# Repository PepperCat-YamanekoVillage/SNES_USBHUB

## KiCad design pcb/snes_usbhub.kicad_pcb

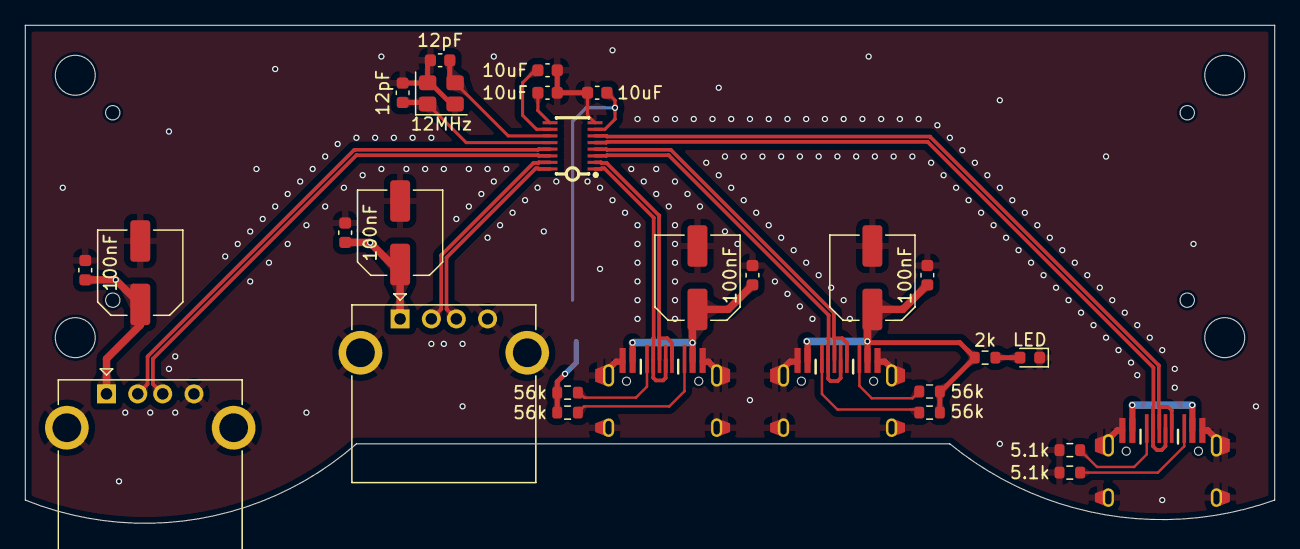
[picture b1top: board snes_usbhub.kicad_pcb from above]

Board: 2 copper layers, 100.0 x 39.9 mm, 36 parts (0 on the bottom side), 23 nets.

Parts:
C1, C3, C21, C23: 100uF; C_Elec_6.3x5.4
C2, C4, C29, C30: 100nF; C_0603_1608Metric
C5, C6: 12pF; C_0603_1608Metric
C7, C8, C9: 10uF; C_0603_1608Metric
D1: LED; LED_0603_1608Metric
H1, H2, H3, H4: MountingHole_3.2mm_M3_ISO7380
H5, H6, H7, H8: toolinghole
J1, J2, J3: USB_C_Connecter; usbc_hand
J8, J9: USB_A; USB_A_Kycon_KUSBX-AS1N-B_Horizontal
R1, R2, R3, R4: 56k; R_0603_1608Metric
R13: 2k; R_0603_1608Metric
R20, R21: 5.1k; R_0603_1608Metric
U3: SL2.1S; SSOP-16_L4.6-W2.6-P0.53-LS4.0-BL
Y1: 12MHz; Crystal_SMD_3225-4Pin_3.2x2.5mm

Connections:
+5V: C1.1, C2.2, C3.1, C4.2, C7.1, C21.1, C23.1, C29.2, C30.2, J1.A4 (VBUS), J2.A4 (VBUS), J3.A4 (VBUS), J8.1 (VBUS), J9.1 (VBUS), R1.2, R2.2, R3.2, R4.2, R13.1, U3.7 (VDD5)
/deviceA1/D+: J8.3 (D+), U3.16 (DP3)
/deviceA1/D-: J8.2 (D-), U3.15 (DM3)
/deviceA2/D+: J9.3 (D+), U3.14 (DP4)
/deviceA2/D-: J9.2 (D-), U3.13 (DM4)
/deviceC1/D+: J3.A6 (D+), J3.B6 (D+), U3.2 (DP2)
/deviceC1/D-: J3.A7 (D-), J3.B7 (D-), U3.1 (DM2)
/deviceC/D+: J2.A6 (D+), J2.B6 (D+), U3.4 (DP1)
/deviceC/D-: J2.A7 (D-), J2.B7 (D-), U3.3 (DM1)
/hub/D+: J1.A6 (D+), J1.B6 (D+), U3.6 (UDP)
/hub/D-: J1.A7 (D-), J1.B7 (D-), U3.5 (UDM)
GND: C1.2, C2.1, C3.2, C4.1, C5.2, C6.1, C7.2, C8.1, C9.1, C21.2, C23.2, C29.1, C30.1, D1.1 (K), J1.A1 (GND), J1.S1 (SHIELD), J2.A1 (GND), J2.S1 (SHIELD), J3.A1 (GND), J3.S1 (SHIELD), J8.4 (GND), J8.5 (Shield), J9.4 (GND), J9.5 (Shield), R20.2, R21.2, U3.8 (VSS), Y1.2, Y1.4
unnamed: D1.2 (A), R13.2
unnamed: J1.A5 (CC1), R20.1
unnamed: J1.B5 (CC2), R21.1
unnamed: J2.A5 (CC1), R1.1
unnamed: J2.B5 (CC2), R2.1
unnamed: J3.A5 (CC1), R3.1
unnamed: J3.B5 (CC2), R4.1
unnamed: C8.2, U3.10 (VDD18)
unnamed: C9.2, U3.9 (VDD33)
unnamed: C5.1, U3.12 (XIN), Y1.1
unnamed: C6.2, U3.11 (XOUT), Y1.3

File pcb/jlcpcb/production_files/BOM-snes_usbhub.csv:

Comment,Designator,Footprint,LCSC,Quantity
100nF,"C2,C29,C30,C4",C_0603_1608Metric,C1525,4
10uF,"C7,C8,C9",C_0603_1608Metric,C19702,3
12MHz,Y1,Crystal_SMD_3225-4Pin_3.2x2.5mm,C9002,1
12pF,"C5,C6",C_0603_1608Metric,C1554,2
2k,R13,R_0603_1608Metric,C4109,1
5.1k,"R20,R21",R_0603_1608Metric,C25905,2
56k,"R1,R2,R3,R4",R_0603_1608Metric,C25796,4
LED,D1,LED_0603_1608Metric,C2286,1
SL2.1S,U3,SSOP-16_L4.6-W2.6-P0.53-LS4.0-BL,C2684433,1
100uF,C1,C_Elec_6.3x5.4,,1
100uF,C3,C_Elec_6.3x5.4,,1
USB_A,J8,USB_A_Kycon_KUSBX-AS1N-B_Horizontal,,1
USB_C_Connecter,J3,usbc_hand,,1
100uF,C21,C_Elec_6.3x5.4,,1
USB_C_Connecter,J2,usbc_hand,,1
100uF,C23,C_Elec_6.3x5.4,,1
USB_C_Connecter,J1,usbc_hand,,1
USB_A,J9,USB_A_Kycon_KUSBX-AS1N-B_Horizontal,,1
